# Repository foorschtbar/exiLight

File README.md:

# ExiLight

A smart light replacement for a Fischer DK2 Rettungszeichenleuchten. Stay tuned.

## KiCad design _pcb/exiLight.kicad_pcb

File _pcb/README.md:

# ExiLight

A smart light replacement for a Fischer DK2 Rettungszeichenleuchten. Stay tuned.

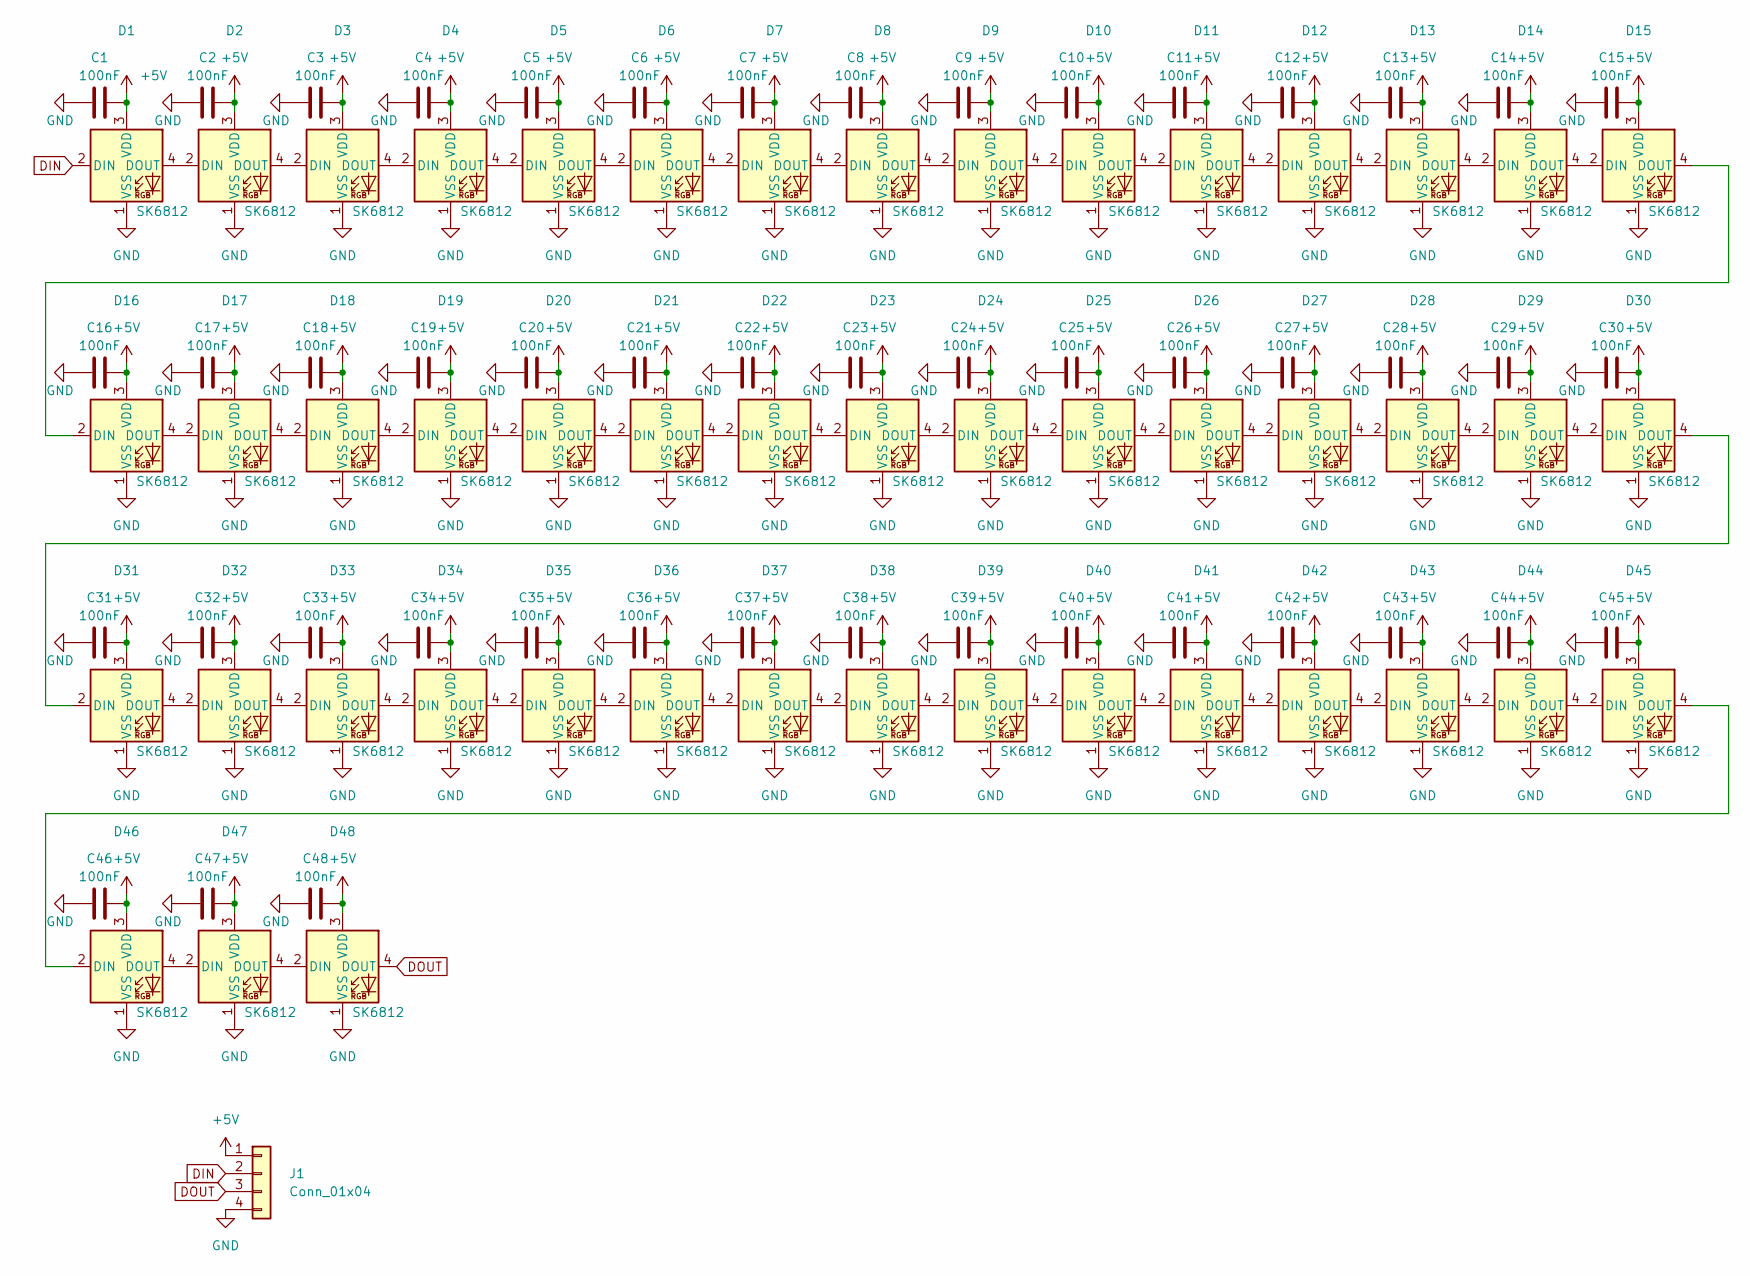
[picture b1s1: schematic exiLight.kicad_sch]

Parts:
C1, C2, C3, C4, C5, C6, C7, C8, C9, C10, C11, C12, C13, C14, C15, C16, C17, C18, C19, C20, C21, C22, C23, C24, C25, C26, C27, C28, C29, C30, C31, C32, C33, C34, C35, C36, C37, C38, C39, C40, C41, C42, C43, C44, C45, C46, C47, C48: 100nF; C_0805_2012Metric_Pad1.18x1.45mm_HandSolder
D1, D2, D3, D4, D5, D6, D7, D8, D9, D10, D11, D12, D13, D14, D15, D16, D17, D18, D19, D20, D21, D22, D23, D24, D25, D26, D27, D28, D29, D30, D31, D32, D33, D34, D35, D36, D37, D38, D39, D40, D41, D42, D43, D44, D45, D46, D47, D48: SK6812; LED_SK6812_PLCC4_5.0x5.0mm_P3.2mm
J1: Conn_01x04

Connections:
+5V: C1.2, C2.2, C3.2, C4.2, C5.2, C6.2, C7.2, C8.2, C9.2, C10.2, C11.2, C12.2, C13.2, C14.2, C15.2, C16.2, C17.2, C18.2, C19.2, C20.2, C21.2, C22.2, C23.2, C24.2, C25.2, C26.2, C27.2, C28.2, C29.2, C30.2, C31.2, C32.2, C33.2, C34.2, C35.2, C36.2, C37.2, C38.2, C39.2, C40.2, C41.2, C42.2, C43.2, C44.2, C45.2, C46.2, C47.2, C48.2, D1.3 (VDD), D2.3 (VDD), D3.3 (VDD), D4.3 (VDD), D5.3 (VDD), D6.3 (VDD), D7.3 (VDD), D8.3 (VDD), D9.3 (VDD), D10.3 (VDD), D11.3 (VDD), D12.3 (VDD), D13.3 (VDD), D14.3 (VDD), D15.3 (VDD), D16.3 (VDD), D17.3 (VDD), D18.3 (VDD), D19.3 (VDD), D20.3 (VDD), D21.3 (VDD), D22.3 (VDD), D23.3 (VDD), D24.3 (VDD), D25.3 (VDD), D26.3 (VDD), D27.3 (VDD), D28.3 (VDD), D29.3 (VDD), D30.3 (VDD), D31.3 (VDD), D32.3 (VDD), D33.3 (VDD), D34.3 (VDD), D35.3 (VDD), D36.3 (VDD), D37.3 (VDD), D38.3 (VDD), D39.3 (VDD), D40.3 (VDD), D41.3 (VDD), D42.3 (VDD), D43.3 (VDD), D44.3 (VDD), D45.3 (VDD), D46.3 (VDD), D47.3 (VDD), D48.3 (VDD), J1.1
DIN: D1.2 (DIN), J1.2
DOUT: D48.4 (DOUT), J1.3
GND: C1.1, C2.1, C3.1, C4.1, C5.1, C6.1, C7.1, C8.1, C9.1, C10.1, C11.1, C12.1, C13.1, C14.1, C15.1, C16.1, C17.1, C18.1, C19.1, C20.1, C21.1, C22.1, C23.1, C24.1, C25.1, C26.1, C27.1, C28.1, C29.1, C30.1, C31.1, C32.1, C33.1, C34.1, C35.1, C36.1, C37.1, C38.1, C39.1, C40.1, C41.1, C42.1, C43.1, C44.1, C45.1, C46.1, C47.1, C48.1, D1.1 (VSS), D2.1 (VSS), D3.1 (VSS), D4.1 (VSS), D5.1 (VSS), D6.1 (VSS), D7.1 (VSS), D8.1 (VSS), D9.1 (VSS), D10.1 (VSS), D11.1 (VSS), D12.1 (VSS), D13.1 (VSS), D14.1 (VSS), D15.1 (VSS), D16.1 (VSS), D17.1 (VSS), D18.1 (VSS), D19.1 (VSS), D20.1 (VSS), D21.1 (VSS), D22.1 (VSS), D23.1 (VSS), D24.1 (VSS), D25.1 (VSS), D26.1 (VSS), D27.1 (VSS), D28.1 (VSS), D29.1 (VSS), D30.1 (VSS), D31.1 (VSS), D32.1 (VSS), D33.1 (VSS), D34.1 (VSS), D35.1 (VSS), D36.1 (VSS), D37.1 (VSS), D38.1 (VSS), D39.1 (VSS), D40.1 (VSS), D41.1 (VSS), D42.1 (VSS), D43.1 (VSS), D44.1 (VSS), D45.1 (VSS), D46.1 (VSS), D47.1 (VSS), D48.1 (VSS), J1.4
unnamed: D1.4 (DOUT), D2.2 (DIN)
unnamed: D2.4 (DOUT), D3.2 (DIN)
unnamed: D3.4 (DOUT), D4.2 (DIN)
unnamed: D4.4 (DOUT), D5.2 (DIN)
unnamed: D5.4 (DOUT), D6.2 (DIN)
unnamed: D6.4 (DOUT), D7.2 (DIN)
unnamed: D7.4 (DOUT), D8.2 (DIN)
unnamed: D8.4 (DOUT), D9.2 (DIN)
unnamed: D9.4 (DOUT), D10.2 (DIN)
unnamed: D10.4 (DOUT), D11.2 (DIN)
unnamed: D11.4 (DOUT), D12.2 (DIN)
unnamed: D12.4 (DOUT), D13.2 (DIN)
unnamed: D13.4 (DOUT), D14.2 (DIN)
unnamed: D14.4 (DOUT), D15.2 (DIN)
unnamed: D15.4 (DOUT), D16.2 (DIN)
unnamed: D16.4 (DOUT), D17.2 (DIN)
unnamed: D17.4 (DOUT), D18.2 (DIN)
unnamed: D18.4 (DOUT), D19.2 (DIN)
unnamed: D19.4 (DOUT), D20.2 (DIN)
unnamed: D20.4 (DOUT), D21.2 (DIN)
unnamed: D21.4 (DOUT), D22.2 (DIN)
unnamed: D22.4 (DOUT), D23.2 (DIN)
unnamed: D23.4 (DOUT), D24.2 (DIN)
unnamed: D24.4 (DOUT), D25.2 (DIN)
unnamed: D25.4 (DOUT), D26.2 (DIN)
unnamed: D26.4 (DOUT), D27.2 (DIN)
unnamed: D27.4 (DOUT), D28.2 (DIN)
unnamed: D28.4 (DOUT), D29.2 (DIN)
unnamed: D29.4 (DOUT), D30.2 (DIN)
unnamed: D30.4 (DOUT), D31.2 (DIN)
unnamed: D31.4 (DOUT), D32.2 (DIN)
unnamed: D32.4 (DOUT), D33.2 (DIN)
unnamed: D33.4 (DOUT), D34.2 (DIN)
unnamed: D34.4 (DOUT), D35.2 (DIN)
unnamed: D35.4 (DOUT), D36.2 (DIN)
unnamed: D36.4 (DOUT), D37.2 (DIN)
unnamed: D37.4 (DOUT), D38.2 (DIN)
unnamed: D38.4 (DOUT), D39.2 (DIN)
unnamed: D39.4 (DOUT), D40.2 (DIN)
unnamed: D40.4 (DOUT), D41.2 (DIN)
unnamed: D41.4 (DOUT), D42.2 (DIN)
unnamed: D42.4 (DOUT), D43.2 (DIN)
unnamed: D43.4 (DOUT), D44.2 (DIN)
unnamed: D44.4 (DOUT), D45.2 (DIN)
unnamed: D45.4 (DOUT), D46.2 (DIN)
unnamed: D46.4 (DOUT), D47.2 (DIN)
unnamed: D47.4 (DOUT), D48.2 (DIN)

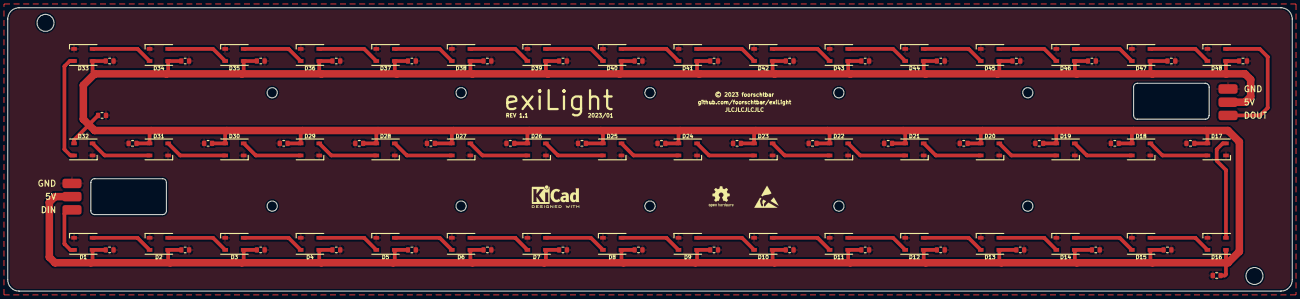
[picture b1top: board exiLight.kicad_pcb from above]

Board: 2 copper layers, 340.0 x 75.0 mm, 96 parts (0 on the bottom side), 49 nets.

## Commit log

2023-01-22 Inital commit
2023-01-22 Add PCB rendering
2023-01-22 Fixed README
2023-01-22 Added Caps

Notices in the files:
_pcb/exiLight.kicad_pcb:
© 2023 foorschtbar
